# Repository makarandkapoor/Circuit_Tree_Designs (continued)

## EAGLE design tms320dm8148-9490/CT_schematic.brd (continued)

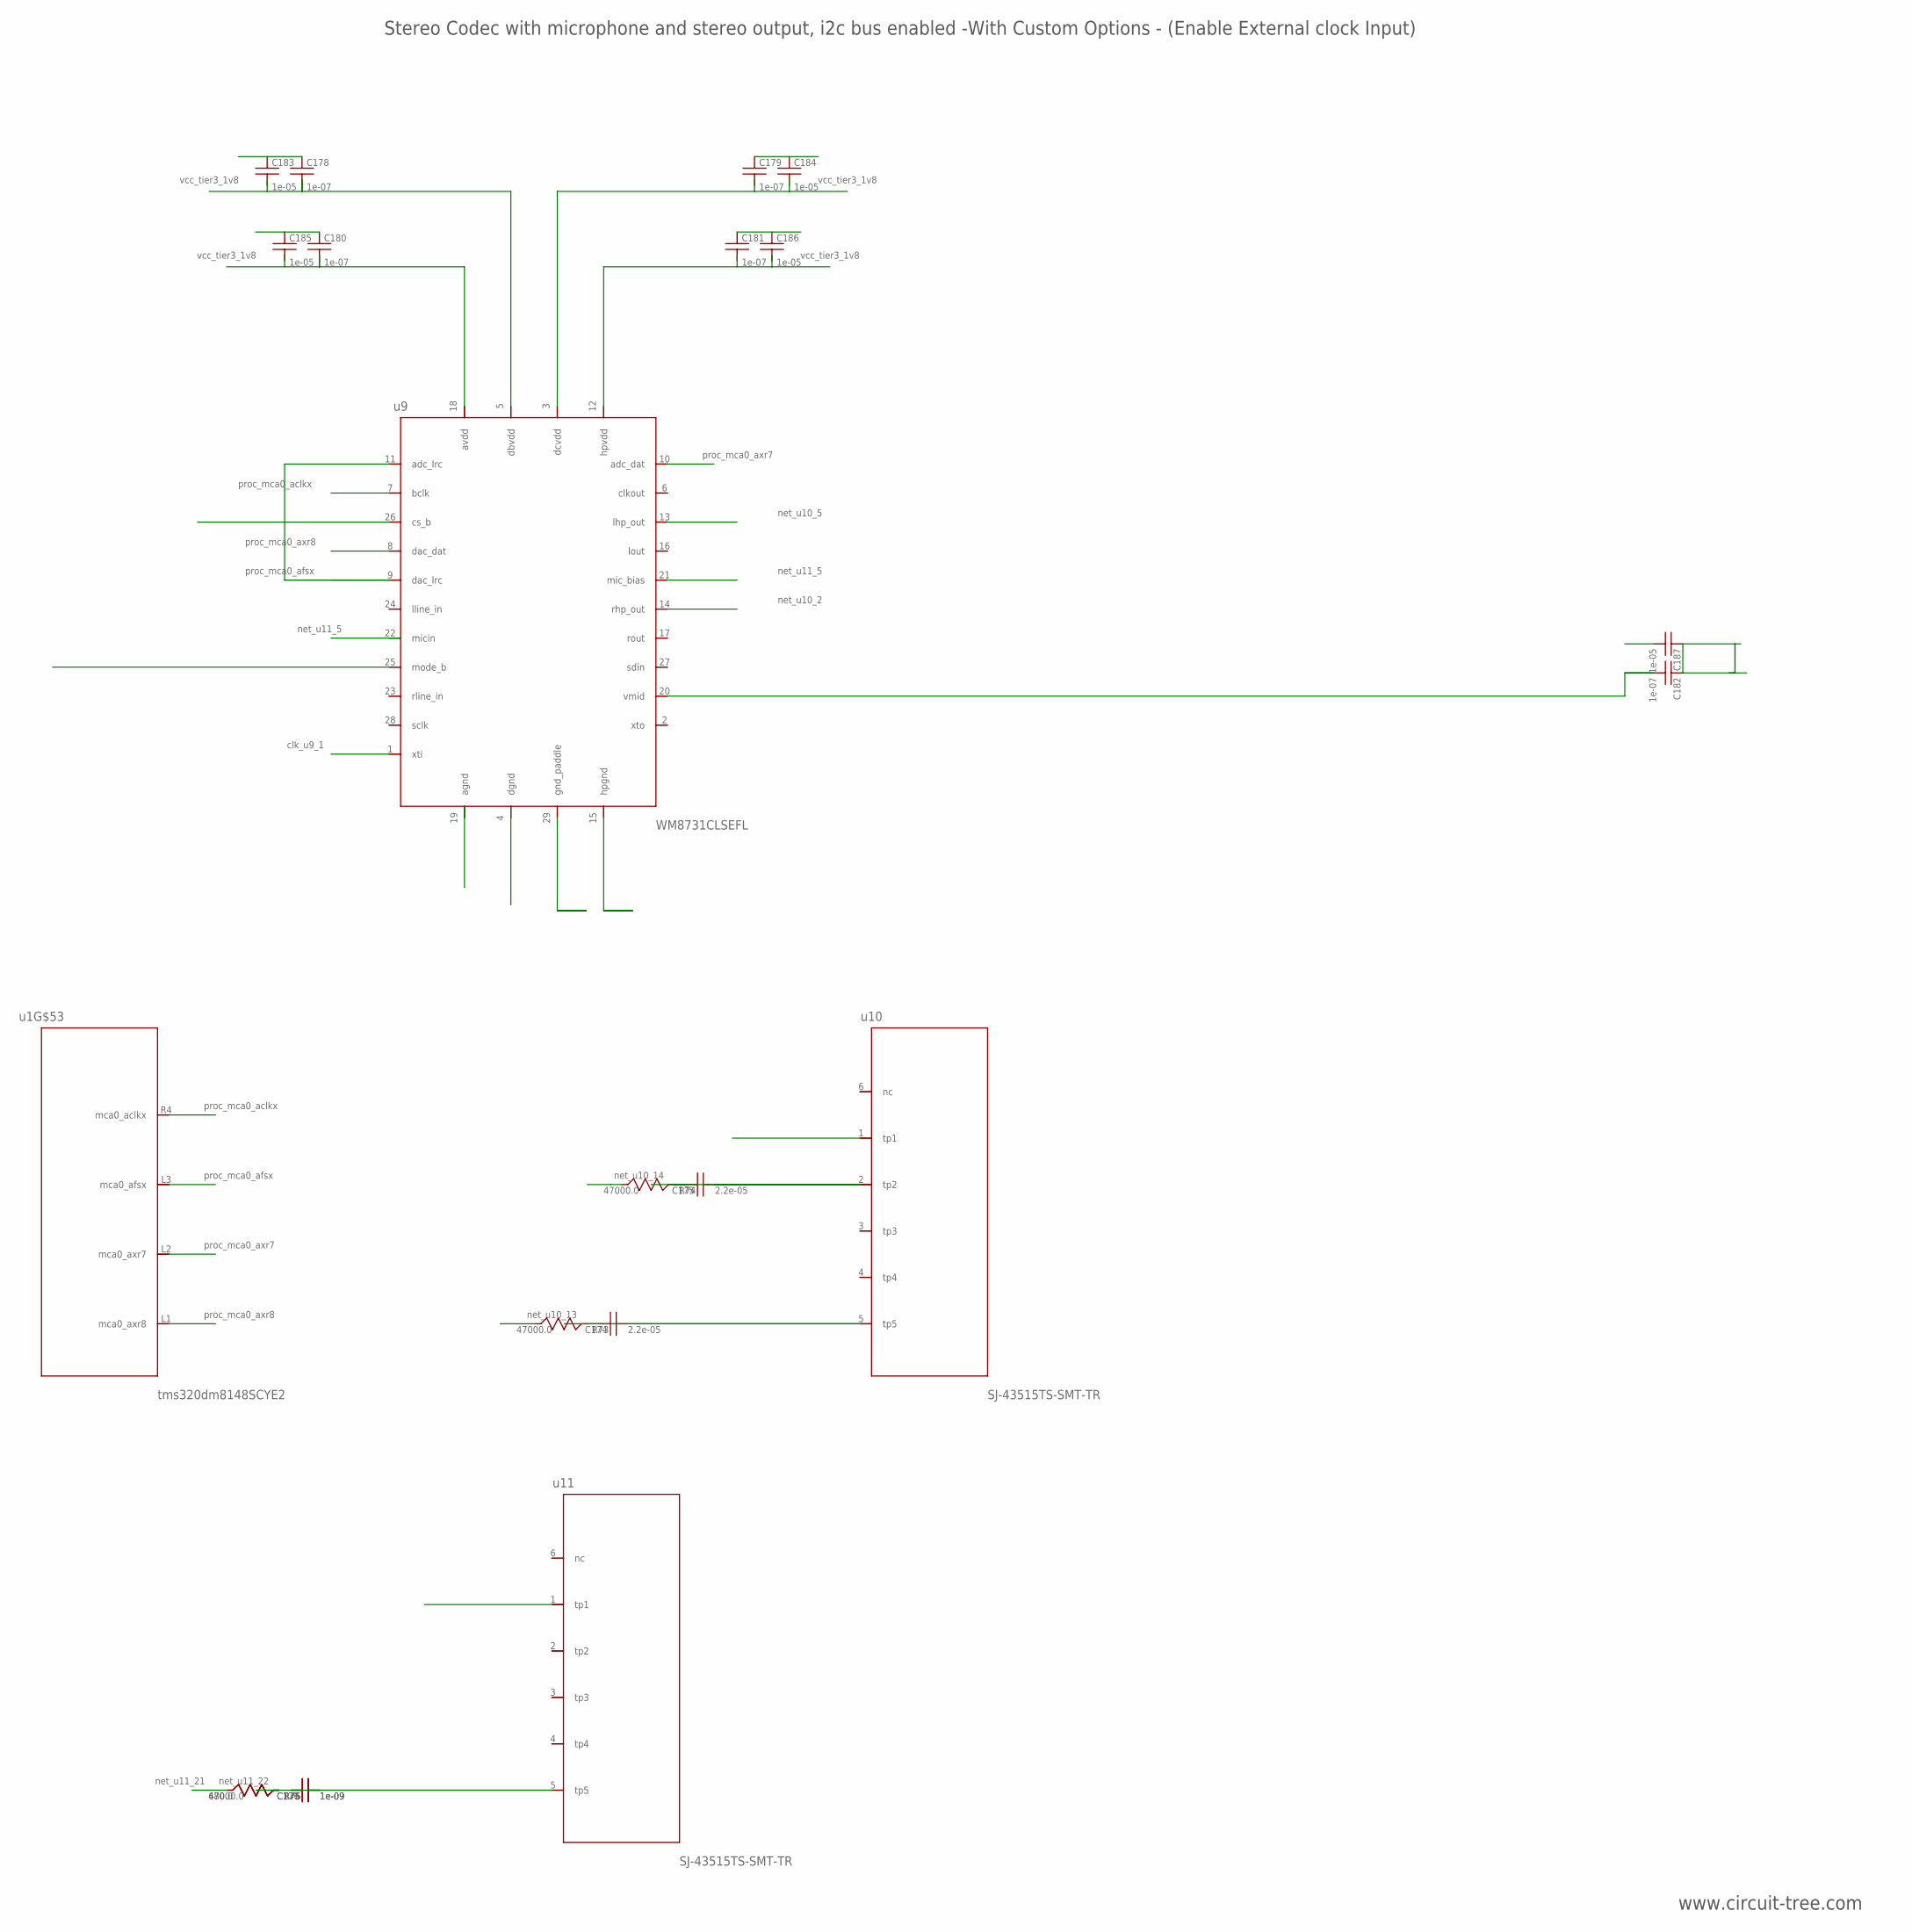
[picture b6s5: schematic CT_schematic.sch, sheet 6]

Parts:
C174, C175: 2.2e-05; C1210
C176, C177: 1e-09; C0402
C178, C179, C180, C181, C182: 1e-07; C0402
C183, C184, C185, C186, C187: 1e-05; C0805
R73, R74, R75: 47000.0; R0603
R76: 680.0; R0603
u1: tms320dm8148SCYE2; BFBGA-684
u9: WM8731CLSEFL; QFN-28
u10, u11: SJ-43515TS-SMT-TR

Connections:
NET_U9_20: C182.1, C187.1, u9.20 (vmid); also elsewhere on the board
NET_U10_2: C175.1, R74.1, u10.2 (tp2); also elsewhere on the board
NET_U10_5: C174.1, R73.1, u10.5 (tp5); also elsewhere on the board
NET_U10_13: C174.2
NET_U10_14: C175.2
NET_U11_5: C176.1, C177.1, R75.1, R76.1, u11.5 (tp5); also elsewhere on the board
NET_U11_21: R76.2
NET_U11_22: C176.2
unnamed: u1.L1 (mca0_axr8), u9.8 (dac_dat)
unnamed: u1.L2 (mca0_axr7), u9.10 (adc_dat)
unnamed: u1.L3 (mca0_afsx), u9.9 (dac_lrc), u9.11 (adc_lrc)
unnamed: u1.R4 (mca0_aclkx), u9.7 (bclk)

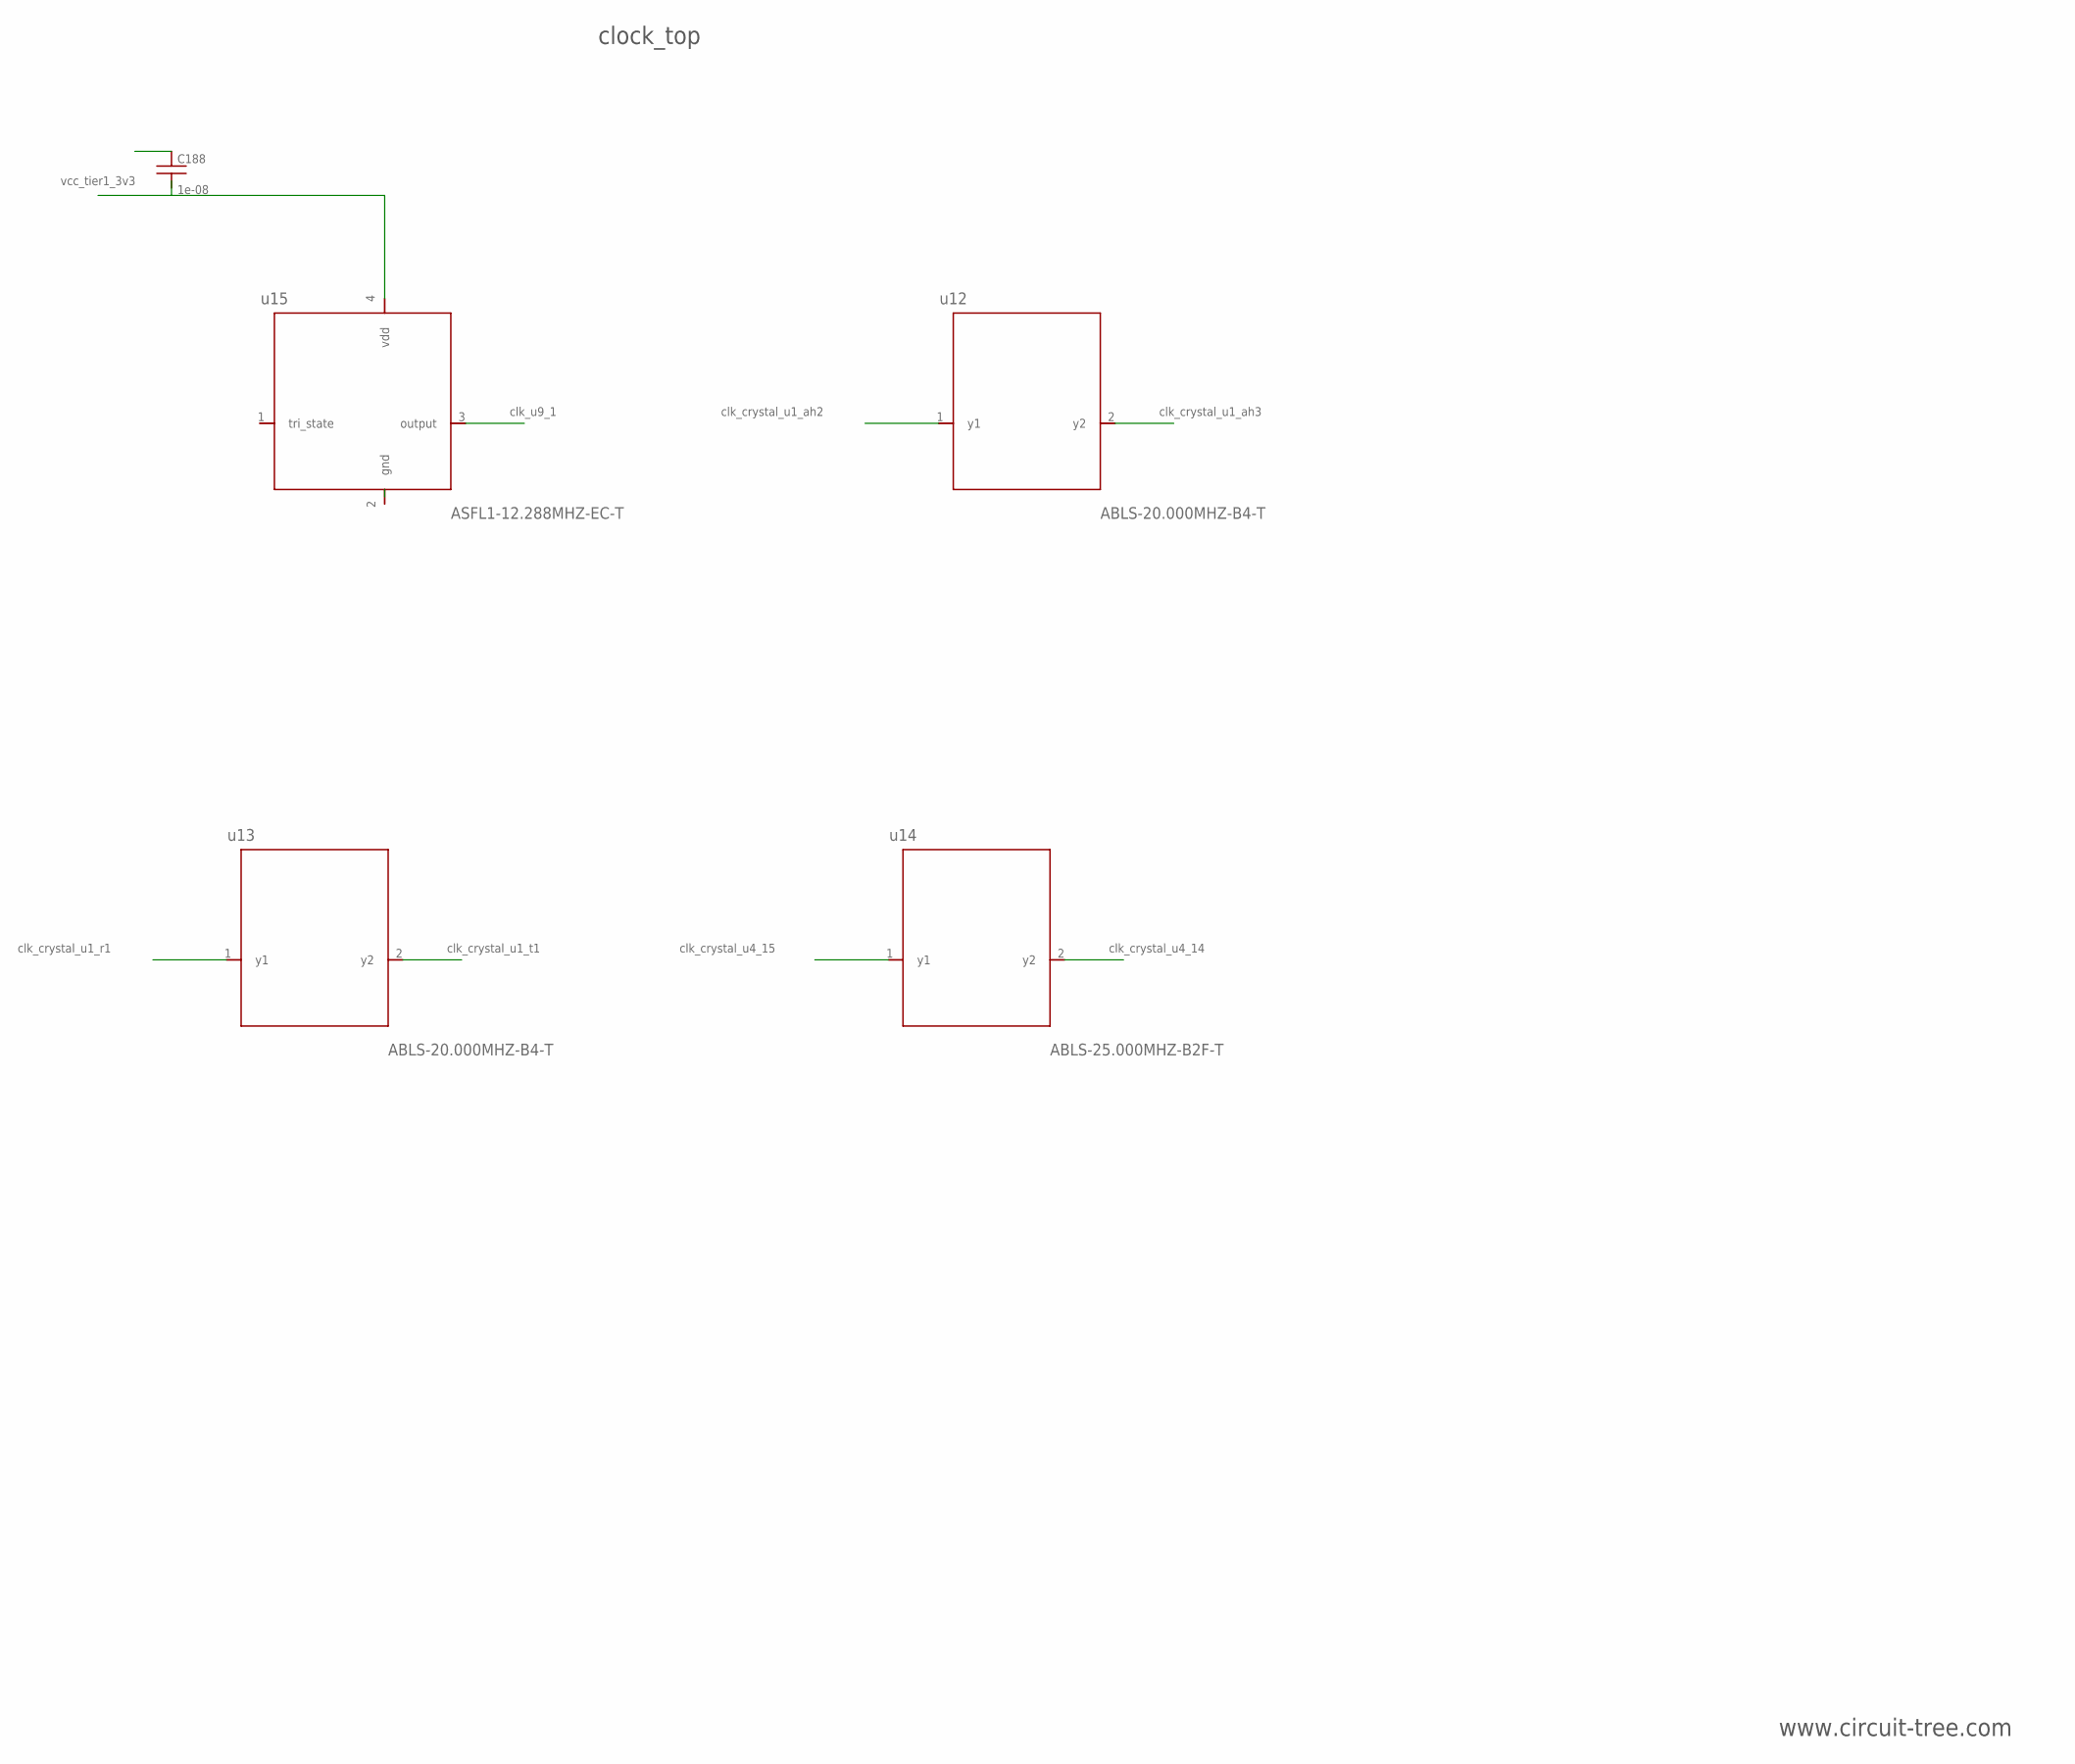
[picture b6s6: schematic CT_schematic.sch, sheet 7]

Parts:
C188: 1e-08; C0402
u12, u13: ABLS-20.000MHZ-B4-T
u14: ABLS-25.000MHZ-B2F-T
u15: ASFL1-12.288MHZ-EC-T; ASFL1

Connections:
VCC_TIER1_3V3: C188.1, u15.4 (vdd); also elsewhere on the board

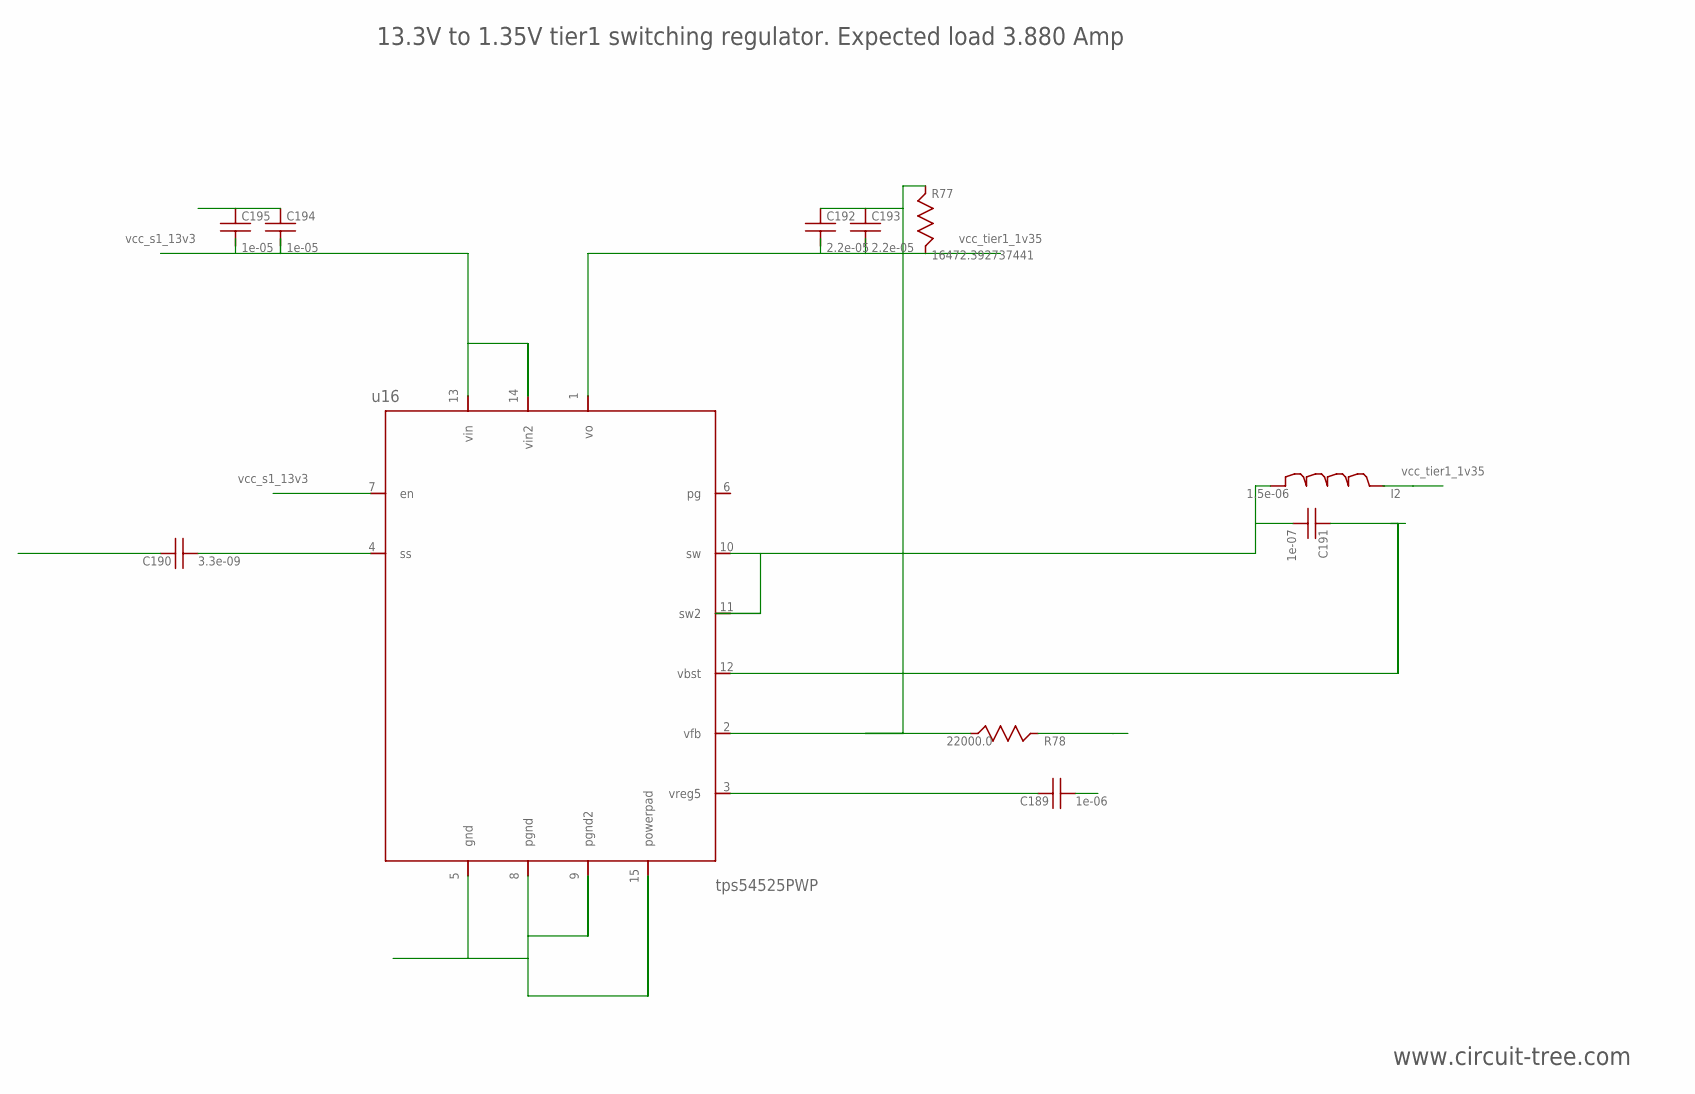
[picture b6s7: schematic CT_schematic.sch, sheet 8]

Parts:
C189: 1e-06; C0603
C190: 3.3e-09; C0402
C191: 1e-07; C0402
C192, C193: 2.2e-05; C1210
C194, C195: 1e-05; C1206
I2: 1.5e-06; IND_PM3316
R77: 16472.392737441; R0603
R78: 22000.0; R0603
u16: tps54525PWP; HTSSOP14

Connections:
NET_U16_2: R77.2, R78.1, u16.2 (vfb); also elsewhere on the board
NET_U16_3: C189.1, u16.3 (vreg5); also elsewhere on the board
NET_U16_4: C190.1, u16.4 (ss); also elsewhere on the board
NET_U16_10: C191.1, I2.1, u16.10 (sw), u16.11 (sw2); also elsewhere on the board
NET_U16_12: C191.2, u16.12 (vbst); also elsewhere on the board
VCC_S1_13V3: C194.1, C195.1, u16.7 (en), u16.13 (vin), u16.14 (vin2); also elsewhere on the board
VCC_TIER1_1V35: C192.1, C193.1, I2.2, R77.1, u16.1 (vo); also elsewhere on the board

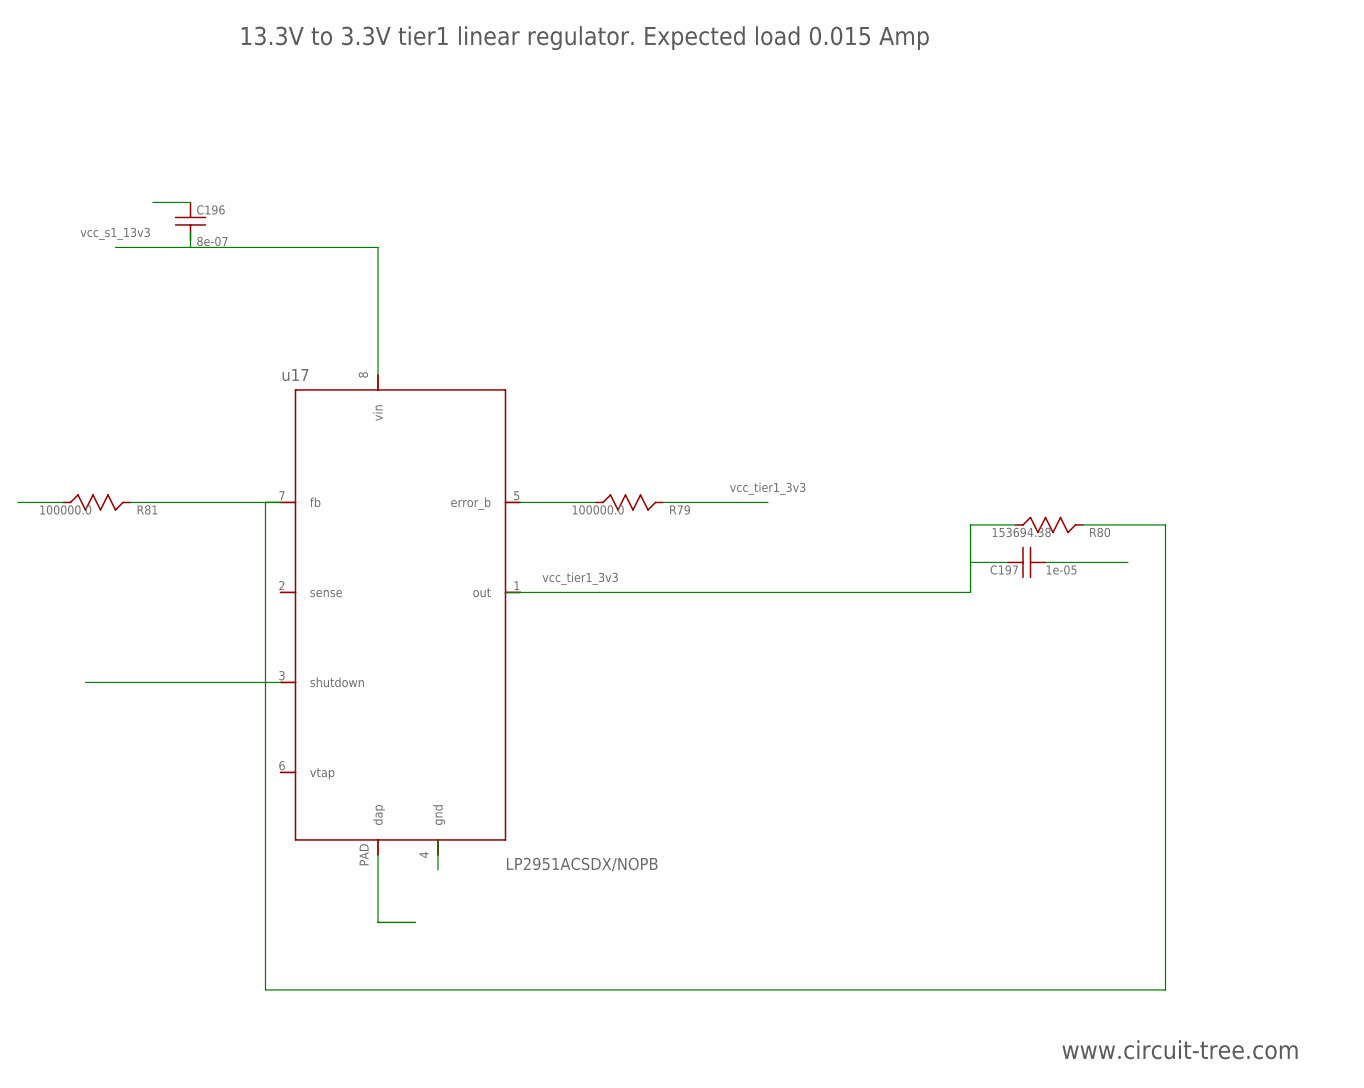
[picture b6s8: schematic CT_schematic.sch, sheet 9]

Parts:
C196: 8e-07; R0603
C197: 1e-05; C1210
R79, R81: 100000.0; R0603
R80: 153694.38; R0603
u17: LP2951ACSDX/NOPB; WSON-8

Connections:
NET_U17_5: R79.1, u17.5 (error_b); also elsewhere on the board
NET_U17_7: R80.2, R81.1, u17.7 (fb); also elsewhere on the board
VCC_S1_13V3: C196.1, u17.8 (vin); also elsewhere on the board
VCC_TIER1_3V3: C197.1, R79.2, R80.1, u17.1 (out); also elsewhere on the board

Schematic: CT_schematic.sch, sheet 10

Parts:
C198: 1e-05; C0805
C199: 1e-06; C0603
C200: 1e-07; C0402
C201: 6.8e-05; 2220
I3: 2.5e-06; DR1040
R82: 20000.0; R0603
R83: 30000.0; R0603
R84: 300000.0; R0603
u18: LTC3601EUD#PBF; QFN-16_EP

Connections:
NET_U18_3: C200.2, I3.1, u18.3 (sw), u18.4 (sw2); also elsewhere on the board
NET_U18_6: C200.1, u18.6 (boost); also elsewhere on the board
NET_U18_7: C199.1, u18.7 (intvcc), u18.12 (ith); also elsewhere on the board
NET_U18_10: R84.1, u18.10 (rt); also elsewhere on the board
NET_U18_11: R82.1, R83.1, u18.11 (fb); also elsewhere on the board
VCC_S2_13V3: C198.1, u18.15 (vin), u18.16 (vin2); also elsewhere on the board

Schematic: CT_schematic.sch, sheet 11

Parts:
C202: 1e-05; C0805
C203: 1e-06; C0603
C204: 1e-07; C0402
C205: 6.8e-05; 2220
I4: 3.8e-06; DR1040
R85: 20000.0; R0603
R86: 13000.0; R0603
R87: 300000.0; R0603
u19: LTC3601EUD#PBF; QFN-16_EP

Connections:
NET_U19_3: C204.2, I4.1, u19.3 (sw), u19.4 (sw2); also elsewhere on the board
NET_U19_6: C204.1, u19.6 (boost); also elsewhere on the board
NET_U19_7: C203.1, u19.7 (intvcc), u19.12 (ith); also elsewhere on the board
NET_U19_10: R87.1, u19.10 (rt); also elsewhere on the board
NET_U19_11: R85.1, R86.1, u19.11 (fb); also elsewhere on the board
VCC_S3_13V3: C202.1, u19.15 (vin), u19.16 (vin2); also elsewhere on the board

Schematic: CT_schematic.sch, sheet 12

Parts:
C206: 1e-05; C0805
C207: 1e-06; C0603
C208: 1e-07; C0402
C209: 6.8e-05; 2220
I5: 3.3e-06; WE-HCI_7030/7040/7050
R88: 20000.0; R0603
R89: 39000.0; R0603
R90: 300000.0; R0603
u20: LTC3601EUD#PBF; QFN-16_EP

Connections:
NET_U20_3: C208.2, I5.1, u20.3 (sw), u20.4 (sw2); also elsewhere on the board
NET_U20_6: C208.1, u20.6 (boost); also elsewhere on the board
NET_U20_7: C207.1, u20.7 (intvcc), u20.12 (ith); also elsewhere on the board
NET_U20_10: R90.1, u20.10 (rt); also elsewhere on the board
NET_U20_11: R88.1, R89.1, u20.11 (fb); also elsewhere on the board
VCC_S3_13V3: C206.1, u20.15 (vin), u20.16 (vin2); also elsewhere on the board

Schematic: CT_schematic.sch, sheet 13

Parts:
C210: 1e-08; C0402
C211, C212: 1e-05; C1210
R91: 100000.0; R0603
R92: 1500.0; R0603
R93: 1000.0; R0603
u21: LP3878SDX-ADJ/NOPB; WSON-8

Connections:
NET_U21_1: C210.1, u21.1 (bypass); also elsewhere on the board
NET_U21_6: R92.2, R93.1, u21.6 (adj); also elsewhere on the board
NET_U21_8: R91.1, u21.8 (shutdown_b); also elsewhere on the board
VCC_S3_13V3: C211.1, R91.2, u21.4 (vin); also elsewhere on the board
VCC_TIER3_2V5: C212.1, R92.1, u21.5 (out); also elsewhere on the board

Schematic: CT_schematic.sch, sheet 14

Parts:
C213: 1e-08; C0402
C214, C215: 1e-05; C1210
R94: 100000.0; R0603
R95: 2231.0; R0603
R96: 1000.0; R0603
u22: LP3878SDX-ADJ/NOPB; WSON-8

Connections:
NET_U22_1: C213.1, u22.1 (bypass); also elsewhere on the board
NET_U22_6: R95.2, R96.1, u22.6 (adj); also elsewhere on the board
NET_U22_8: R94.1, u22.8 (shutdown_b); also elsewhere on the board
VCC_S3_13V3: C214.1, R94.2, u22.4 (vin); also elsewhere on the board
VCC_TIER3_3V3: C215.1, R95.1, u22.5 (out); also elsewhere on the board

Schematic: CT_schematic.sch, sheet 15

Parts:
C216: 8e-07; R0603
C217: 1e-05; C1210
R97, R99: 100000.0; R0603
R98: 153694.38; R0603
u23: LP2951ACSDX/NOPB; WSON-8

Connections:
NET_U23_5: R97.1, u23.5 (error_b); also elsewhere on the board
NET_U23_7: R98.2, R99.1, u23.7 (fb); also elsewhere on the board
VCC_S4_13V3: C216.1, u23.8 (vin); also elsewhere on the board
VCC_TIER4_3V3: C217.1, R97.2, R98.1, u23.1 (out); also elsewhere on the board

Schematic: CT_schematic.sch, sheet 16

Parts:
C218: 1e-07; C0402
C219: 2.2e-06; C0603
C220: 2.45e-08; R0603
C221: 2.8258362168397e-09; R0603
C222: 7.105e-09; R0603
R100, R102, R103, R108, R109, R110, R111, R112: 10000.0; R0603
R101: 75000.0; R0603
R104, R105, R106, R107: 95300.0; R0603
R113: 110000.0; R0603
u24: LTC2928CUHF#PBF; QFN-38_UHF
u25, u26, u27, u28: IRF8306MTRPbF; IRF8306MTRPBF

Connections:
NET_U24_3: R109.1, u24.3 (v1); also elsewhere on the board
NET_U24_6: R104.1, u24.6 (rt1); also elsewhere on the board
NET_U24_7: R105.1, u24.7 (rt2); also elsewhere on the board
NET_U24_8: R106.1, u24.8 (rt3); also elsewhere on the board
NET_U24_9: R107.1, u24.9 (rt4); also elsewhere on the board
NET_U24_16: R108.1, R113.1, u24.16 (on); also elsewhere on the board
NET_U24_18: R103.1, u24.18 (done_b); also elsewhere on the board
NET_U24_19: R102.1, u24.19 (flt_b), u24.20 (ov_b); also elsewhere on the board
NET_U24_21: R100.1, R101.1, u24.21 (rst_b); also elsewhere on the board
NET_U24_22: C218.1, R100.2, R102.2, R103.2, u24.11 (sqt2), u24.22 (vcc); also elsewhere on the board
NET_U24_26: C221.1, u24.26 (stmr); also elsewhere on the board
NET_U24_27: C220.1, u24.27 (ptmr); also elsewhere on the board
NET_U24_28: C222.1, u24.28 (rtmr); also elsewhere on the board
NET_U24_30: R112.1, u24.30 (v4); also elsewhere on the board
NET_U24_32: R111.1, u24.32 (v3); also elsewhere on the board
NET_U24_38: R110.1, u24.38 (v2); also elsewhere on the board
unnamed: u24.2 (en1), u25.3 (gate)
unnamed: u24.29 (en4), u28.3 (gate)
unnamed: u24.31 (en3), u27.3 (gate)
unnamed: u24.37 (en2), u26.3 (gate)
unnamed: u25.4 (source), u25.5 (source2)
unnamed: u26.4 (source), u26.5 (source2)
unnamed: u27.4 (source), u27.5 (source2)
unnamed: u28.4 (source), u28.5 (source2)
VCC_13V3: C219.1, R113.2, u24.23 (hvcc), u25.1 (drain), u25.2 (drain2), u25.6 (drain3), u25.7 (drain4), u26.1 (drain), u26.2 (drain2), u26.6 (drain3), u26.7 (drain4), u27.1 (drain), u27.2 (drain2), u27.6 (drain3), u27.7 (drain4), u28.1 (drain), u28.2 (drain2), u28.6 (drain3), u28.7 (drain4); also elsewhere on the board

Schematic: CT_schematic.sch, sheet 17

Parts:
C223, C224: 0.0001; EXV-9H
j1: PJ-037B; PJ-037B_PACKAGE

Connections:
VCC_13V3: C223.1, C224.1, j1.1; also elsewhere on the board

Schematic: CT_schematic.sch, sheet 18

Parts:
C225, C226, C227: 1e-08; C0402
u29: 4-1437565-2; SW_4-1437565-2
u30: Q65110A2395; LGM67K-G1J2-24-Z
u31, u32, u33: nc7sz125m5x

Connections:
unnamed: u29.1 (pole1), u29.2 (pole12)
unnamed: u29.3 (pole2), u29.4 (pole22)
unnamed: u31.2 (a), u32.2 (a), u33.2 (a)
VCC_TIER1_3V3: C225.1, C226.1, C227.1, u31.5 (vcc), u32.5 (vcc), u33.5 (vcc); also elsewhere on the board

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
